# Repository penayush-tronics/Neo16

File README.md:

# Neo16

A 4x4 matrix panel of 16 addressable LEDs, which can be used to display small graphics, animations, or keyboard characters. These addressable LEDs (also refered to as NeoPixels) are RGB and so can take more than one colour. These panels can also be 'daisy-chained' together, so that many panels can be used at once. The biggest feature is how it only needs one data pin from a microcontroller/dev board to start displaying. There are multiple sizes available. 

# How to use the Neo16

Here is a 3D labelled diagram of the panel:

On the top right corner, there are 4 headers. They are voltage in (VIN), data in (DIN), ground (GND), and data out (DOUT), in that order from left to right.

Connect power to the VIN and GND pins accordingly; it can take 3.3V or 5V, but make sure your DIN pin input from the microcontroller/dev board matches this voltage (for example: VIN-5V then DIN-5V). Connect DIN to any one digital pin on the microcontroller/dev board. And that's about it for the wiring; it is really simple to hook up. 

For connecting many panels in series, setup the first panel as mentioned above. Then connect the subsequent panels to power accordingly. Then, use a jumper or a wire to connect the DOUT pin on the main, first panel (which is connected to the microcontroller) to the DIN pin on the next panel. Continue this chain of DOUT to DIN for as many times as needed (do not worry about limits, as at this scale the limits are very far away.)

## Programming
### Usign Neo16 Programmer website: 
The Neo16 comes with a [programmer website](https://penayush-tronics.github.io/Neo16/) where you can choose colours, set brightness of the LEDs, and make patterns on a digital copy of the 4x4 matrix of LED, and convert it into Arduino Code. Here is the interface: 

In the center is the matrix. On the top there are settings such as colour and brightness. You can also choose how many boards are daisy-chained together and program them at once. 

To select patterns, click on the cells of the matrix which you want to turn on. 

Click Generate to generate the code. Copy it into Arduino IDE, upload and see it on the Neo16!

#### An example sketch for arduino IDE along with an arduino board can be found [here](Neo16_Example)

**NOTE: This code uses the Adafruit_Neopixel library, and so it needs to be installed in your IDE. Also, this uses digital pin 9 on arduino for Data IN, but you can change this.**

### Programming by yourself
 When programming for this panel, keep in mind the LED matrix is in a specific order. The first LED is the top left corner, and then it continues down the column as 2,3,4. The 5th led then is the adjacent LED in the next column, and then 6,7,8 is up the column. Then it continues, 'snaking' up and down each column. If this is confusing, just remember the order is like how you write the letter ' W '.

# What are Addressable LEDs?
  
  Addressable LEDs are like those smart LED bulbs at home, which have RGB colours. These LEDs are much smaller and usually for multi-colour pixel displays. They are called 'addressable' as you can assign each LED's colour individually, so each pixel can be a seperate colour if needed. The coolest feature is how the data pins of these LEDs can be connected in series, and then still each LED is individually addressable. If you want to know about how this works in detail, you can learn about it [here](https://www.youtube.com/watch?v=2tTsV290nTo).

# Schematics

Here are the schematics for this board:

Schematics available in the [Schematics folder](PCB/Schematics)

# PCB and sizes

There are currently 2 sizes available:
  - panel with 5mmx5mm addressable LEDs (Large size)
  - panel with 2mmx2mm addressable LEDs (Small size)

Large size:
  
  PCB in Kicad-

  Front side-

  Back side-

Small size:
  
  PCB in Kicad-

  Front side-

  Back side-

All PCB Gerbers of all sizes available in [PCB folder](PCB), [Gerbers directory](PCB/Gerbers_and_KicadPCB)

# Video Demo

https://github.com/user-attachments/assets/8053cdf7-2f21-4381-b544-3c394bac34a4

# Why I made this board

Recently, I had an idea for a personal project, and I needed these addressable LEDs for that project. So, I requried small panels for personal use as well as for testing purposes. Yet, I was unable to find a suitable 4x4 matrix for my purposes, and other alternatives were bigger and way too expensive. So, I chose to make one myself; not just for myself but, also for anyone else looking for a small 4x4 matrix of these addressable LEDs (especially the 2mm version).

# Bill of Materials

This BOM is for 1 panel, except for the PCB as it has minimum quantity of 5.

This same BOM is available in [Neo16BOM.csv](Neo16 BOM.csv)

| Sl No. | Component Description | Qty | Price (INR) | Ext Price (INR) | Link |
| :---: | :--- | :---: | :---: | :---: | :--- |
| **1** | WS2812B SMD2020 Addressable RGB LED (for 2mm large size) | 16 | 7.65 | 122.40 | [Quartz Components](https://quartzcomponents.com/products/ws2812b-smd2020-addressable-rgb-pixel-led-smd-package?variant=45110136668394) |
| **2** | WS2812B SMD5050 Addressable RGB LED (for 5mm large size) | 16 | 3.60 | 57.60 | [Quartz Components](https://quartzcomponents.com/products/ws2812b-smd5050-addressable-rgb-led-neopixel-led?pr_prod_strat=jac&pr_rec_id=f8f2799bf&pr_rec_pid=8521263513834&pr_ref_pid=8521726165226&pr_seq=uniform) |
| **3** | 1000nF 50V 0805 X7R SMD Capacitor (Pack of 5 Pieces) | 4 | 13.50 | 60.00 | [Quartz Components](https://quartzcomponents.com/products/1uf-1000nf-50v-0805-x7r-smd-capacitor-pack-of-5-pieces?variant=43526976504042) |
| **4** | 470 $\Omega$ 5% SMD Resistor 0805 (Pack of 20 Pieces) | 1 | 8.00 | 8.00 | [Quartz Components](https://quartzcomponents.com/products/470ohm-470e-5-smd-resistor-0805-pack-of-20-pieces?variant=43515854749930) |
| **5** | TLJA107M006R0800 100uF 6.3V CASE-A-3216-18(mm) Tantalum Capacitors ROHS (for 2mm small size) | 1 | 25.00 | 25.00 | [Robu.in](https://robu.in/product/tlja107m006r0800-kyocera-avx-100uf-6-3v-800m%cf%89100khz-%c2%b120-case-a-3216-18mm-tantalum-capacitors-rohs/) |
| **6** | UUD0J101MCL1GS 100uF 6.3V SMD, D6.3xL5.8mm Aluminum Electrolytic Capacitors - SMD ROHS (for 5mm large size) | 1 | 31.00 | 31.00 | [Robu.in](https://robu.in/product/uud0j101mcl1gs-nichicon-100uf-6-3v-115ma120hz-%c2%b120-smdd6-3xl5-8mm-aluminum-electrolytic-capacitors-smd-rohs/) |
| **7** | PCB Fabrication | 5 | 159.80 | 943 (799 + 18% tax) | [Lion Circuits](https://www.lioncircuits.com/) |
| **8** | 4-pin Header (optional) | 1 | 2.00 | 2.00 | [Robu.in](https://robu.in/product/hb-ph3-25414pb2gop-hanbo-gold-250v-3a-direct-insert-2-54mm-4p-6mm-40%e2%84%83105%e2%84%83-3mm-2-54mm-brass-black-single-row-1x4p-2-54mm-pluginp2-54mm-pin-headers-rohs/) |

Total per board cost varies from size to size:
  
  For the **small 2mm size**: 217.4 INR for components + 188.6 INR for PCB -> **406 INR   ~ $4.30 USD**
  
  For the **large 5mm size**: 158.6 INR for components + 188.6 INR for PCB -> **347.2 INR ~ $3.65 USD**

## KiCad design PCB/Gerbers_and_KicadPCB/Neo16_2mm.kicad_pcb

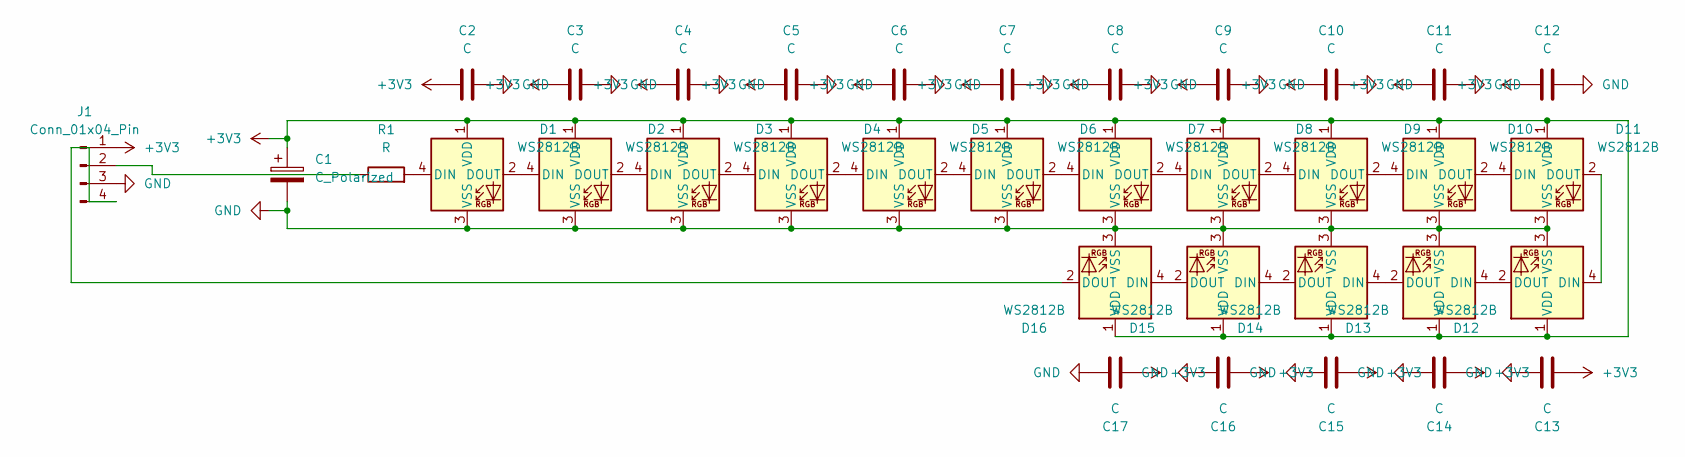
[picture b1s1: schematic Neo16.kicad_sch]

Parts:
C1: C_Polarized; CP_EIA-3216-18_Kemet-A_HandSolder
C2, C3, C4, C5, C6, C7, C8, C9, C10, C11, C12, C13, C14, C15, C16, C17: C; C_0805_2012Metric_Pad1.18x1.45mm_HandSolder
D1, D2, D3, D4, D5, D6, D7, D8, D9, D10, D11, D12, D13, D14, D15, D16: WS2812B; LED_WS2812B-2020_PLCC4_2.0x2.0mm
J1: Conn_01x04_Pin; PinHeader_1x04_P2.54mm_Vertical
R1: R; R_0805_2012Metric_Pad1.20x1.40mm_HandSolder

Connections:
+3V3: C1.1, C2.1, C3.1, C4.1, C5.1, C6.1, C7.1, C8.1, C9.1, C10.1, C11.1, C12.1, C13.1, C14.1, C15.1, C16.1, C17.1, D1.1 (VDD), D2.1 (VDD), D3.1 (VDD), D4.1 (VDD), D5.1 (VDD), D6.1 (VDD), D7.1 (VDD), D8.1 (VDD), D9.1 (VDD), D10.1 (VDD), D11.1 (VDD), D12.1 (VDD), D13.1 (VDD), D14.1 (VDD), D15.1 (VDD), D16.1 (VDD), J1.1
GND: C1.2, C2.2, C3.2, C4.2, C5.2, C6.2, C7.2, C8.2, C9.2, C10.2, C11.2, C12.2, C13.2, C14.2, C15.2, C16.2, C17.2, D1.3 (VSS), D2.3 (VSS), D3.3 (VSS), D4.3 (VSS), D5.3 (VSS), D6.3 (VSS), D7.3 (VSS), D8.3 (VSS), D9.3 (VSS), D10.3 (VSS), D11.3 (VSS), D12.3 (VSS), D13.3 (VSS), D14.3 (VSS), D15.3 (VSS), D16.3 (VSS), J1.3
unnamed: D1.4 (DIN), R1.2
unnamed: D1.2 (DOUT), D2.4 (DIN)
unnamed: D2.2 (DOUT), D3.4 (DIN)
unnamed: D3.2 (DOUT), D4.4 (DIN)
unnamed: D4.2 (DOUT), D5.4 (DIN)
unnamed: D5.2 (DOUT), D6.4 (DIN)
unnamed: D6.2 (DOUT), D7.4 (DIN)
unnamed: D7.2 (DOUT), D8.4 (DIN)
unnamed: D8.2 (DOUT), D9.4 (DIN)
unnamed: D9.2 (DOUT), D10.4 (DIN)
unnamed: D10.2 (DOUT), D11.4 (DIN)
unnamed: D11.2 (DOUT), D12.4 (DIN)
unnamed: D12.2 (DOUT), D13.4 (DIN)
unnamed: D13.2 (DOUT), D14.4 (DIN)
unnamed: D14.2 (DOUT), D15.4 (DIN)
unnamed: D15.2 (DOUT), D16.4 (DIN)
unnamed: D16.2 (DOUT), J1.4
unnamed: J1.2, R1.1

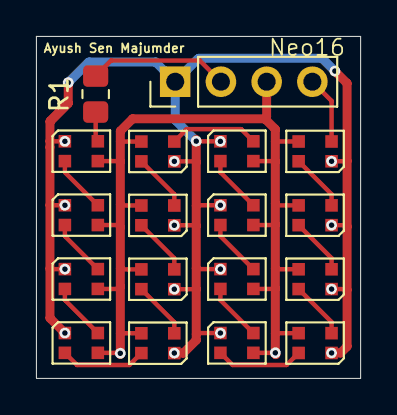
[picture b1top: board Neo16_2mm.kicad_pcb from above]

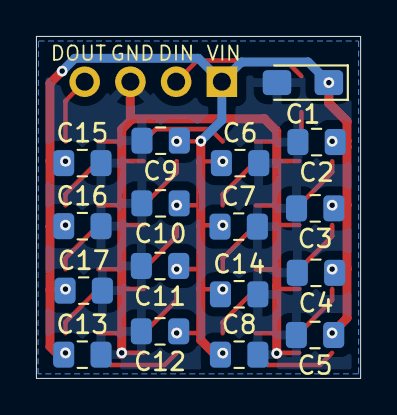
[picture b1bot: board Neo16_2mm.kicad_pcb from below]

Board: 2 copper layers, 18.0 x 19.0 mm, 35 parts (17 on the bottom side), 20 nets.

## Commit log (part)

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2026-06-11 Added schematics and PCB files from Kicad
2026-06-11 Added image of schematic
2026-06-11 Added images of PCB in kicad and 3d view.
2026-06-11 Added PCB images in Kicad and 3d viewer
2026-06-11 Updated readme to final version; added diagram and cover image.
2026-06-11 Updated clarity in readme
2026-06-11 more clarity
2026-06-11 fixed some errors in readme
2026-06-11 Added BOM file
2026-06-11 fixed spelling in readme
2026-06-12 Added new updated BOM
2026-06-12 upadated readme BOM for sizes, and added per-board cost sorted by size.
2026-06-24 added pick and place position file
